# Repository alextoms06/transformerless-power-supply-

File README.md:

# TRANSFORMERLESS AC to DC Converter PCB

Tools:
- KiCad 9

Features:
- Bridge rectifier (1N4007)
- 7805 voltage regulator
- LED power indicator
- Filter capacitors (RECTANGULAR RADIAL AND DISK FOOTPRINT)
- 1N4001 THT DIODE
- 2 SCREW TERMINALS FOR INPUT AC AND OUTPUT DC 
- RESISTOR AXIAL
Files:
- Schematic
- PCB layout
- Gerber files

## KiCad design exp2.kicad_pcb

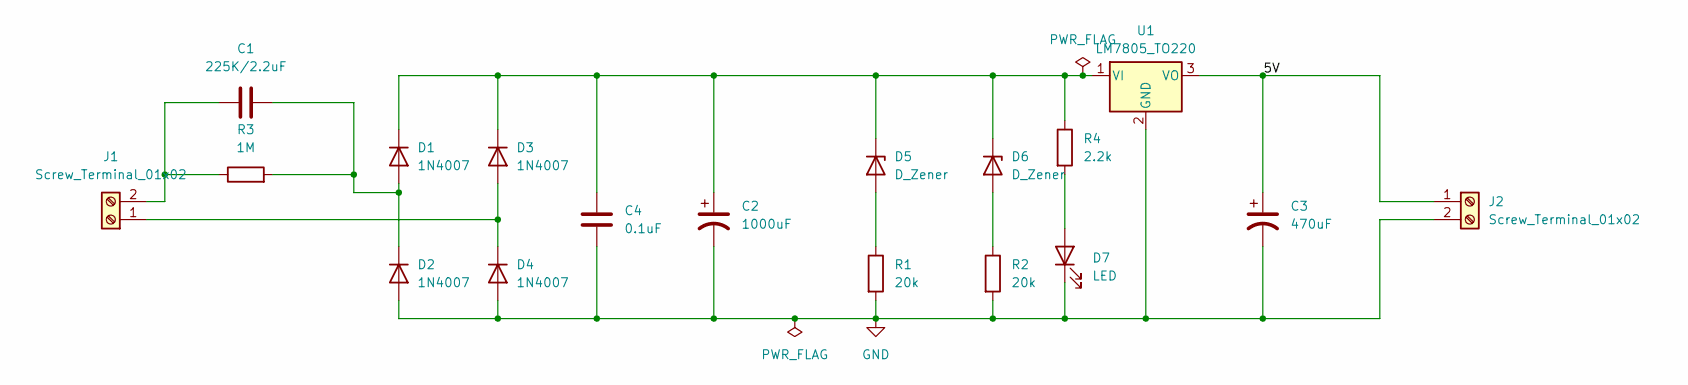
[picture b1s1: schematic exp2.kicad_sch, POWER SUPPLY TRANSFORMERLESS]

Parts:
C1: 225K/2.2uF; C_Rect_L10.0mm_W5.0mm_P5.00mm_P7.50mm
C2: 1000uF; CP_Radial_D10.0mm_P5.00mm
C3: 470uF; CP_Radial_D10.0mm_P5.00mm
C4: 0.1uF; C_Disc_D8.0mm_W2.5mm_P5.00mm
D1, D2, D3, D4: 1N4007; D_DO-41_SOD81_P10.16mm_Horizontal
D5, D6: D_Zener; D_A-405_P7.62mm_Horizontal
D7: LED; LED_D5.0mm
J1, J2: Screw_Terminal_01x02; TerminalBlock_bornier-2_P5.08mm
R1, R2: 20k; R_Axial_DIN0207_L6.3mm_D2.5mm_P7.62mm_Horizontal
R3: 1M; R_Axial_DIN0207_L6.3mm_D2.5mm_P7.62mm_Horizontal
R4: 2.2k; R_Axial_DIN0207_L6.3mm_D2.5mm_P7.62mm_Horizontal
U1: LM7805_TO220; TO-220-3_Vertical

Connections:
/5V: C3.1, J2.1, U1.3 (VO)
GND: C2.2, C3.2, C4.2, D2.2 (A), D4.2 (A), D7.1 (K), J2.2, R1.2, R2.2, U1.2 (GND)
unnamed: C1.2, D1.2 (A), D2.1 (K), R3.2
unnamed: C2.1, C4.1, D1.1 (K), D3.1 (K), D5.1 (K), D6.1 (K), R4.1, U1.1 (VI)
unnamed: D3.2 (A), D4.1 (K), J1.1
unnamed: D5.2 (A), R1.1
unnamed: D6.2 (A), R2.1
unnamed: D7.2 (A), R4.2
unnamed: C1.1, J1.2, R3.1

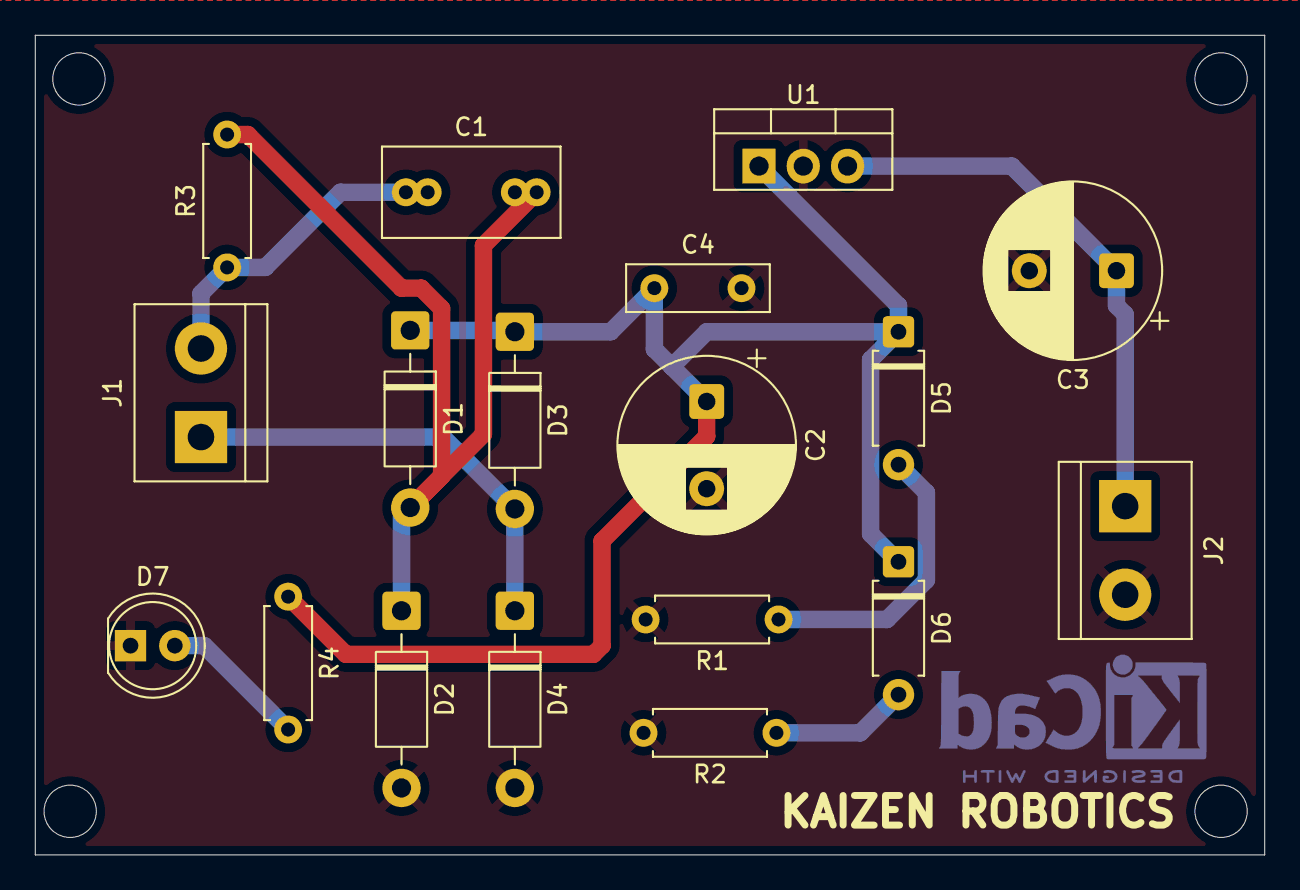
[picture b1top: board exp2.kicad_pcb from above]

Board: 2 copper layers, 70.5 x 47.0 mm, 18 parts (0 on the bottom side), 9 nets.

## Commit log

2026-06-10 Add files via upload
    GERBER ZIP FILE
